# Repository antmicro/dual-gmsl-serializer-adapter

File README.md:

# Dual Camera to GMSL Serializer CSI Adapter

Copyright (c) 2024-2025 [Antmicro](https://www.antmicro.com)

## Overview

This project provides open hardware design files for the Dual Camera to GMSL Serializer CSI Adapter. 
The board is designed to receive two MIPI CSI-2 x2 signals from the [OV5640 Dual Camera Board](https://github.com/antmicro/ov5640-dual-camera-board) and output them to two [GMSL Serializer Boards](https://github.com/antmicro/gmsl-serializer).
The on-board power distribution circuit allows the Dual Camera Board to be powered by one of the selected serializer boards.
The design files were prepared using KiCad 8.x.

## Key features

* 50-pin FFC input connector for the Dual Camera Board connection, exposing two 4-lane MIPI CSI-2 interfaces
* Two 50-pin FFC output connectors for the GMSL Serializer Boards, each supporting a 4-lane MIPI CSI-2 interface
* Two QWIIC connectors for seamless integration of additional I²C devices

## Project structure

The main directory includes KiCad PCB project files, a LICENSE, and a README.
The remaining files are stored in the following directories:

* ``doc`` - contains schematics in PDF format
* ``assets`` - contains visual assets for showcasing this design on [Open Hardware Portal](https://openhardware.antmicro.com) and [System Designer](https://designer.antmicro.com/welcome)

## Licensing

This project is published under the [Apache-2.0](LICENSE) license.

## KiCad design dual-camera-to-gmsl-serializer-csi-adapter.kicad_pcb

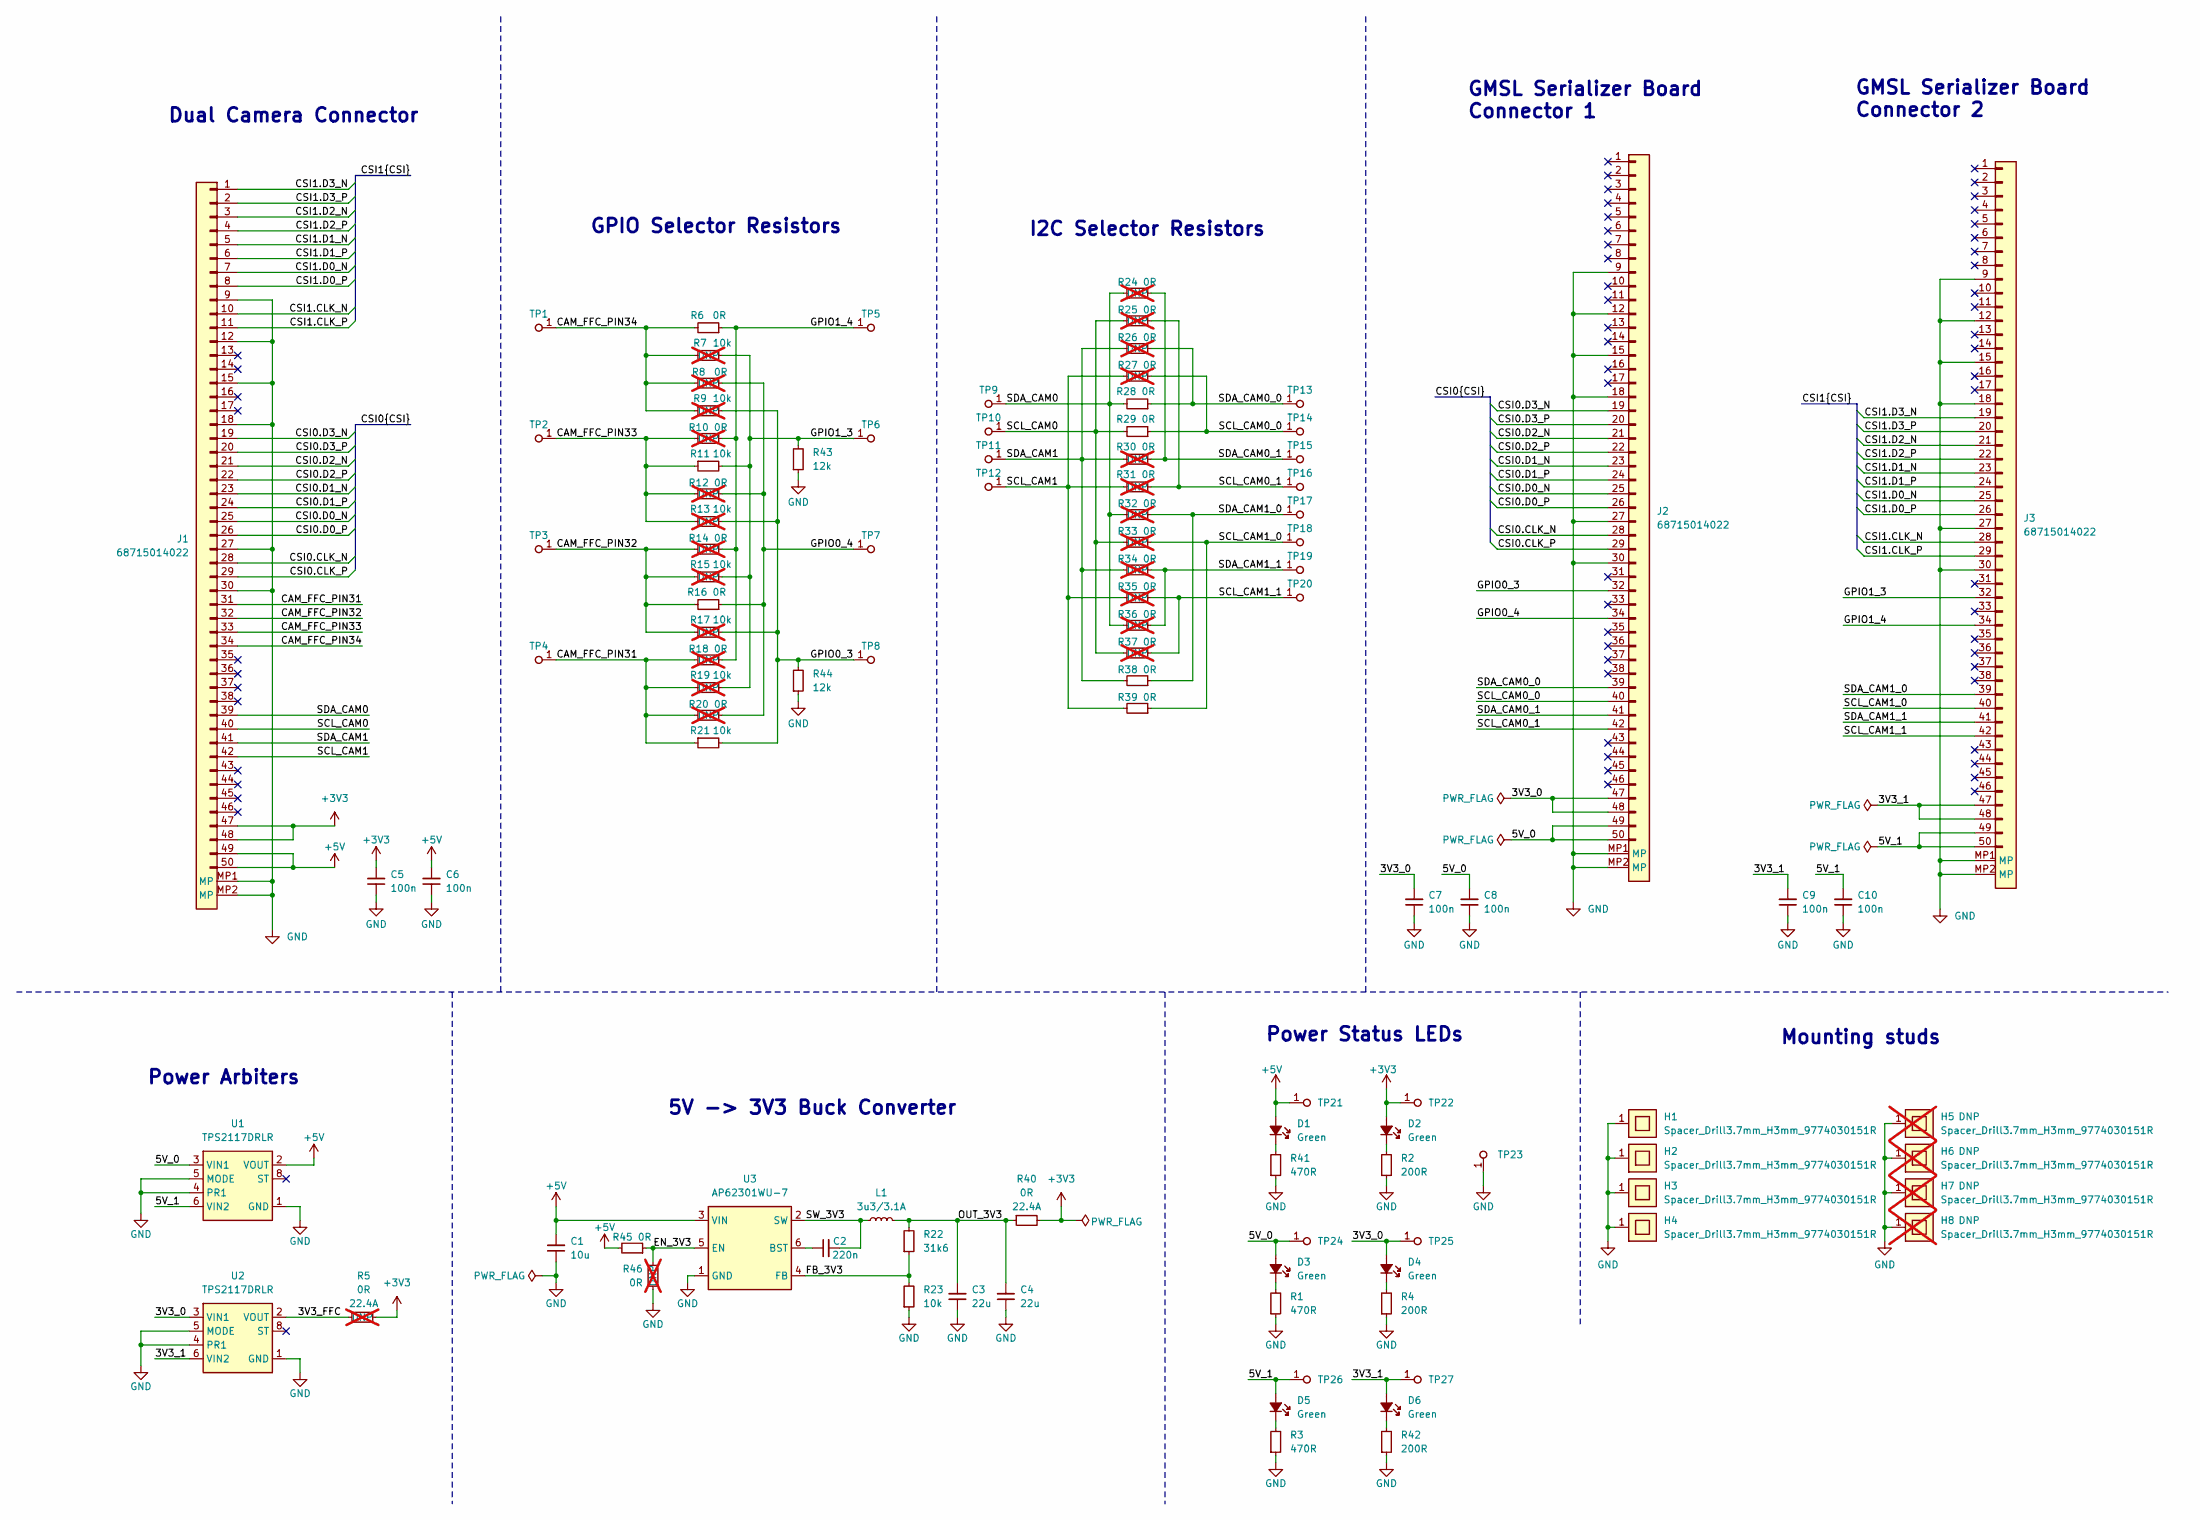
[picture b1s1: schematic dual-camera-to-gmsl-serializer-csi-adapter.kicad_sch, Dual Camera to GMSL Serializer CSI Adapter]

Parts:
C1: C_10u_25V_0603; C_0603_1608Metric; Voltage 25V; MPN C1608X5R1E106M080AC
C2: C_220n_0402; C_0402_1005Metric; MPN CC0402KRX5R6BB224
C3, C4: C_22u_0402; C_0402_1005Metric; MPN GRM158R60J226ME01D
C5, C6, C7, C8, C9, C10: C_100n_0402; C_0402_1005Metric; Voltage 50V; MPN GRM155R61H104KE14D
D1, D2, D3, D4, D5, D6: LED_G_0603_LTST-C190GKT; LED_0603_1608Metric_G; MPN LTST-C190GKT
H1, H2, H3, H4: Spacer_Drill3.7mm_H3mm_9774030151R; MPN 9774030151R
H5, H6, H7, H8: Spacer_Drill3.7mm_H3mm_9774030151R; MPN 9774030151R; not fitted
J1, J2, J3: Conn_FFC_WE_68715014022; Conn_FFC_WE_68715014x22; MPN 68715014022
L1: L_3u3_3.1A_Bourns-SRP3212A; L_Bourns-SRP3212A; MPN SRP3212-3R3M
R1, R3, R41: R_470R_0402; R_0402_1005Metric; Tolerance 1%; MPN CR0402-FX-4700GLF
R2, R4, R42: R_200R_0402; R_0402_1005Metric; Tolerance 1%; MPN CR0402-FX-2000GLF
R5: R_0R_22.4A_0603; R_0603_1608Metric; Tolerance template_tolerance; MPN PMR03EZPJ000; not fitted
R6, R16, R28, R29, R38, R39, R45: R_0R_0402; R_0402_1005Metric; MPN ERJ2GE0R00X
R7, R9, R13, R15, R17, R19: R_10k_0402; R_0402_1005Metric; Tolerance 1%; MPN CR0402-FX-1002GLF; not fitted
R8, R10, R12, R14, R18, R20, R24, R25, R26, R27, R30, R31, R32, R33, R34, R35, R36, R37, R46: R_0R_0402; R_0402_1005Metric; MPN ERJ2GE0R00X; not fitted
R11, R21, R23: R_10k_0402; R_0402_1005Metric; Tolerance 1%; MPN CR0402-FX-1002GLF
R22: R_31k6_0402; R_0402_1005Metric; Tolerance 1%; MPN CR0402-FX-3162GLF
R40: R_0R_22.4A_0603; R_0603_1608Metric; Tolerance template_tolerance; MPN PMR03EZPJ000
R43, R44: R_12k_0402; R_0402_1005Metric; Tolerance 1%; MPN CR0402-FX-1202GLF
TP1, TP2, TP3, TP4, TP5, TP6, TP7, TP8, TP9, TP10, TP11, TP12, TP13, TP14, TP15, TP16, TP17, TP18, TP19, TP20, TP21, TP22, TP23, TP24, TP25, TP26, TP27: TP_1.5mm_SMD; TP_SMD_1.5mm
U1, U2: TPS2117DRLR; SOT-583; MPN TPS2117DRLR
U3: AP62301_TSOT; TSOT23-6; MPN AP62301WU-7

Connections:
+3V3: C5.2, D2.2 (A), J1.47, J1.48, R5.2, R40.2, TP22.1
+5V: C1.2, C6.2, D1.2 (A), J1.49, J1.50, R45.2, TP21.1, U1.2 (VOUT), U1.7 (VOUT), U3.3 (VIN)
/3V3_0: C7.2, D4.2 (A), J2.47, J2.48, TP25.1, U2.3 (VIN1)
/3V3_1: C9.2, D6.2 (A), J3.47, J3.48, TP27.1, U2.6 (VIN2)
/3V3_FFC: R5.1, U2.2 (VOUT), U2.7 (VOUT)
/5V_0: C8.2, D3.2 (A), J2.49, J2.50, TP24.1, U1.3 (VIN1)
/5V_1: C10.2, D5.2 (A), J3.49, J3.50, TP26.1, U1.6 (VIN2)
/CAM_FFC_PIN31: J1.31, R18.2, R19.1, R20.2, R21.1, TP4.1
/CAM_FFC_PIN32: J1.32, R14.2, R15.1, R16.2, R17.1, TP3.1
/CAM_FFC_PIN33: J1.33, R10.2, R11.1, R12.2, R13.1, TP2.1
/CAM_FFC_PIN34: J1.34, R6.2, R7.1, R8.2, R9.1, TP1.1
/CSI0.CLK_N: J1.28, J2.28
/CSI0.CLK_P: J1.29, J2.29
/CSI0.D0_N: J1.25, J2.25
/CSI0.D0_P: J1.26, J2.26
/CSI0.D1_N: J1.23, J2.23
/CSI0.D1_P: J1.24, J2.24
/CSI0.D2_N: J1.21, J2.21
/CSI0.D2_P: J1.22, J2.22
/CSI0.D3_N: J1.19, J2.19
/CSI0.D3_P: J1.20, J2.20
/CSI1.CLK_N: J1.10, J3.28
/CSI1.CLK_P: J1.11, J3.29
/CSI1.D0_N: J1.7, J3.25
/CSI1.D0_P: J1.8, J3.26
/CSI1.D1_N: J1.5, J3.23
/CSI1.D1_P: J1.6, J3.24
/CSI1.D2_N: J1.3, J3.21
/CSI1.D2_P: J1.4, J3.22
/CSI1.D3_N: J1.1, J3.19
/CSI1.D3_P: J1.2, J3.20
/EN_3V3: R45.1, R46.1, U3.5 (EN)
/FB_3V3: R22.1, R23.2, U3.4 (FB)
/GPIO0_3: J2.32, R9.2, R13.2, R17.2, R21.2, R44.2, TP8.1
/GPIO0_4: J2.34, R8.1, R12.1, R16.1, R20.1, TP7.1
/GPIO1_3: J3.32, R7.2, R11.2, R15.2, R19.2, R43.2, TP6.1
/GPIO1_4: J3.34, R6.1, R10.1, R14.1, R18.1, TP5.1
/OUT_3V3: C3.2, C4.2, L1.2, R22.2, R40.1
/SCL_CAM0: J1.40, R25.2, R29.2, R33.2, R37.2, TP10.1
/SCL_CAM0_0: J2.40, R27.1, R29.1, TP14.1
/SCL_CAM0_1: J2.42, R25.1, R31.1, TP16.1
/SCL_CAM1: J1.42, R27.2, R31.2, R35.2, R39.2, TP12.1
/SCL_CAM1_0: J3.40, R33.1, R39.1, TP18.1
/SCL_CAM1_1: J3.42, R35.1, R37.1, TP20.1
/SDA_CAM0: J1.39, R24.2, R28.2, R32.2, R36.2, TP9.1
/SDA_CAM0_0: J2.39, R26.1, R28.1, TP13.1
/SDA_CAM0_1: J2.41, R24.1, R30.1, TP15.1
/SDA_CAM1: J1.41, R26.2, R30.2, R34.2, R38.2, TP11.1
/SDA_CAM1_0: J3.39, R32.1, R38.1, TP17.1
/SDA_CAM1_1: J3.41, R34.1, R36.1, TP19.1
/SW_3V3: C2.2, L1.1, U3.2 (SW)
GND: C1.1, C3.1, C4.1, C5.1, C6.1, C7.1, C8.1, C9.1, C10.1, H1.1, H2.1, H3.1, H4.1, H5.1, H6.1, H7.1, H8.1, J1.9, J1.12, J1.15, J1.18, J1.27, J1.30, J1.MP1 (MP), J1.MP2 (MP), J2.9, J2.12, J2.15, J2.18, J2.27, J2.30, J2.MP1 (MP), J2.MP2 (MP), J3.9, J3.12, J3.15, J3.18, J3.27, J3.30, J3.MP1 (MP), J3.MP2 (MP), R1.1, R2.1, R3.1, R4.1, R23.1, R41.1, R42.1, R43.1, R44.1, R46.2, TP23.1, U1.1 (GND), U1.4 (PR1), U1.5 (MODE), U2.1 (GND), U2.4 (PR1), U2.5 (MODE), U3.1 (GND)
unnamed: D1.1 (C), R41.2
unnamed: D2.1 (C), R2.2
unnamed: D3.1 (C), R1.2
unnamed: D4.1 (C), R4.2
unnamed: D5.1 (C), R3.2
unnamed: D6.1 (C), R42.2
unnamed: C2.1, U3.6 (BST)

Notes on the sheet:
Power Status LEDs
Power Arbiters
5V -> 3V3 Buck Converter
I2C Selector Resistors
GPIO Selector Resistors
GMSL Serializer Board Connector 1
Dual Camera Connector
GMSL Serializer Board Connector 2
Mounting studs

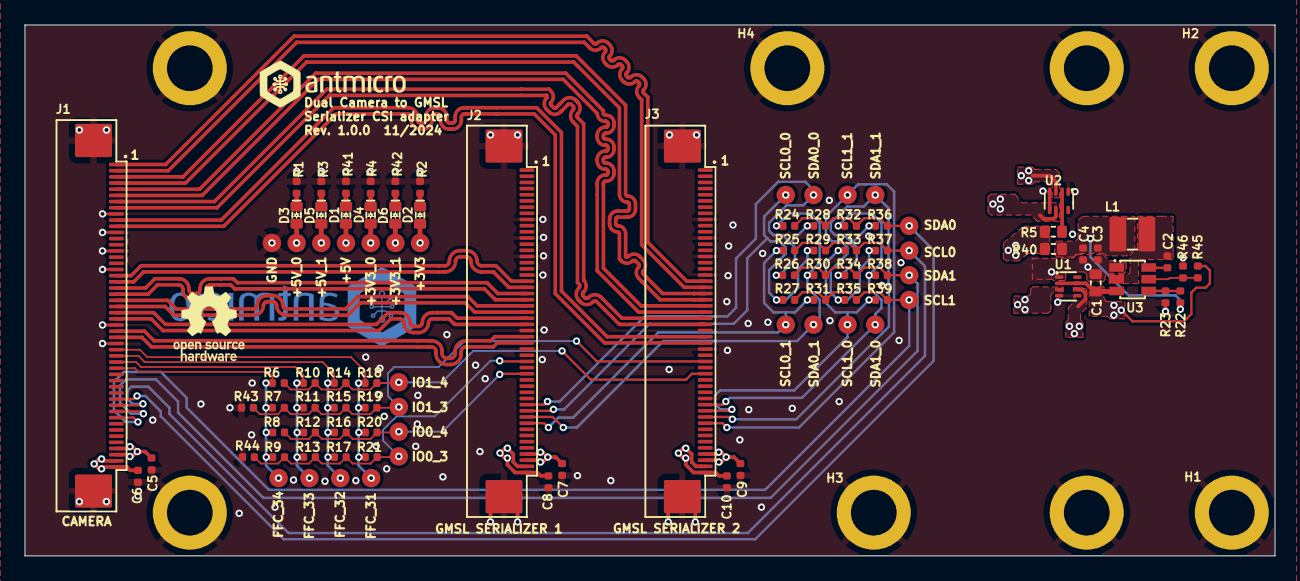
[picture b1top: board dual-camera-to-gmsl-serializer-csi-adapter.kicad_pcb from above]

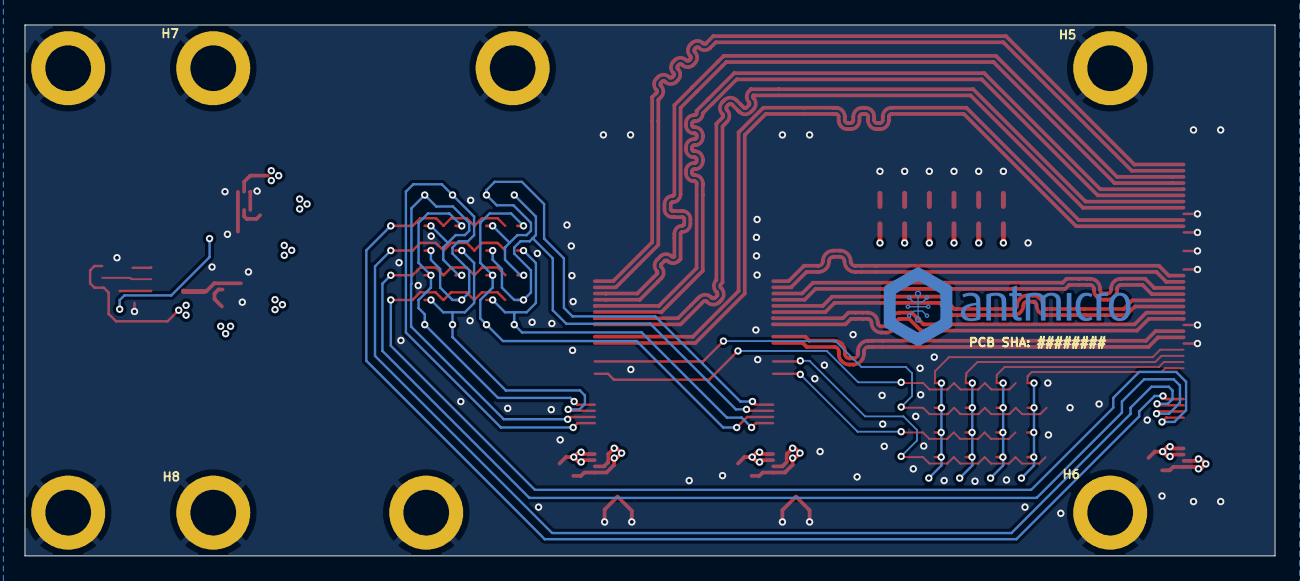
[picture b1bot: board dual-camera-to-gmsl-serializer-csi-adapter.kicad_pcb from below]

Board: 4 copper layers, 101.2 x 43.0 mm, 104 parts (4 on the bottom side), 59 nets.

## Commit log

2024-11-22 [#69172] Add project, license and readme
2024-11-22 [#69172] Add connectors and buck converter to schematics
2024-11-25 [#69172] Add resistor selectors
2024-11-26 [#69172] Transfer schematic onto pcb
2024-11-26 [#69172] Rotate FFC connectors
2024-11-26 [#69172] Add power planes
2024-11-27 [#69172] Update schematics
2024-11-27 [#69172] Update PCB
2024-11-27 [#69172] Update components
2024-11-27 [#69172] Add post-review fixes
2024-11-27 [#69172] Update name in readme
2024-11-27 [#69172] Update README
2024-11-27 [#69172] Clean ERC, add GND vias
2024-11-28 [#69172] Fix width issue
2024-11-28 [#69172] Add assets and doc
2024-11-28 [#69474] Fix silkscreen
2024-11-28 [#69474] Update README
2024-11-28 [#69474] Update assets and doc
2024-11-29 README: Add 3DVis
2024-12-18 [#70359] Move camera connector to bottom side
2024-12-19 [#70359] PCB: Extend PCB width
2025-02-17 [#70359] PCB: Align spacers with camera board
2025-02-17 [#70359] PCB: Add camera board mechanical mockup
2025-02-17 [#70359] PCB: Rotate 180deg and move J1
2025-02-17 [#70359] Add TODOs after first review
2025-02-17 [#70359] PCB: Rotate board
2025-02-17 [#70359] PCB: Remove legacy HS tracks
2025-02-17 [#70359] PCB: Add fastening holes
2025-02-17 [#70359] PCB: Update OV5640 mounting holes
2025-02-17 [#70359] Schematic: Resolve I2C mapping
2025-02-17 [#72052] Add connector alignment dimensions
2025-02-17 [#70359] Schematic: Add I2C Qwiic connectors
2025-02-17 [#72052] Route low-speed signals
2025-02-17 [#70359] Schematic: Swap J2 with J3
2025-02-17 [#70359] Schematic: Add OSHW & Antmicro logos
2025-02-17 [#72052] Resolve 5V0, 5V1, 3V0, 3V1 routing
2025-02-17 [#72052] Fix HS clearance
2025-02-17 [#72052] Align low-speed signals
2025-02-17 [#70359] PCB: Try initial routing
2025-02-17 [#72052] restore removed comment arrow
2025-02-17 [#70359] PCB: Cleanup legacy tracks/vias
2025-02-17 [#70359] PCB: Swap J1&J2 power planes
2025-02-17 [#72052] Resolve 5V,3V3 routing
2025-02-17 [#70359] Schematic: Resolve GPIO naming
2025-02-17 [#70359] PCB: Add 100Zout and 100Zinner netclasses
2025-02-17 [#72052] Move J2 and route CSI1
2025-02-17 [#72052] Route and tune CSI0
2025-02-17 [#70359] PCB: Add GND testpoints to both sides
2025-02-17 [#72052] Add camera spacers to BOM
2025-02-17 [#70924] Link ov step in pcb
2025-02-17 [#70359] PCB: Add stackup table
2025-02-17 [#72052] Clean-up and align components
2025-02-17 [#72052] Tune CSI1
2025-02-17 [#70359] PCB: Set stackup to ec-defined-impedance-4L
2025-02-17 [#70924] Add ov camera module step
2025-02-17 [#70359] PCB: Position TPs and logos
2025-02-17 [#72052] Widen GND tracks
2025-02-17 [#72052] Update CSI routing
2025-02-17 [#72052] Increase HS to power zones spacing
2025-02-17 [#72052] Update readme
2025-02-17 [#72052] Improve 5V & 3V breakout
2025-02-17 [#72052] Update readme copyright
2025-02-17 [#72052] Extend power planes and add GND fill on IN2
2025-02-17 [#72052] Clean DRC
2025-02-17 [#72052] Update OHP assets
2025-02-17 [#72052] Update 5V plane
2025-02-17 [#72052] Update Z90 net class
2025-02-17 [#72052] Remove GND fills on top & bot
2025-02-17 [#72052] Widen 3V30 plane on breakout
2025-02-17 [#72052] Remove duplicated dimension object
2025-02-17 [#72052] Remove redundant vias on CSI
2025-02-17 [#72052] Remove local library
2025-02-17 [#72052] Add HS fill keep-out zone
2025-02-17 [#72052] Fix netclass name
2025-02-17 [#72052] Fix connections to power planes
2025-02-17 [#72052] Adjust README.md for publishing
2025-02-17 [#72052] Add supply gnd zone
2025-02-17 [#72052] Increase spacing on CSI1 breakout
2025-02-18 [#70359] Tweak routing, DRC clean
2025-02-18 [#70359] README: Update structure
2025-02-18 [#70359] Re-generate schematic
2025-02-18 [#70359] README update
2025-03-13 [#74504] Flip the design

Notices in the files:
parts and their libraries:
License: Apache-2.0
